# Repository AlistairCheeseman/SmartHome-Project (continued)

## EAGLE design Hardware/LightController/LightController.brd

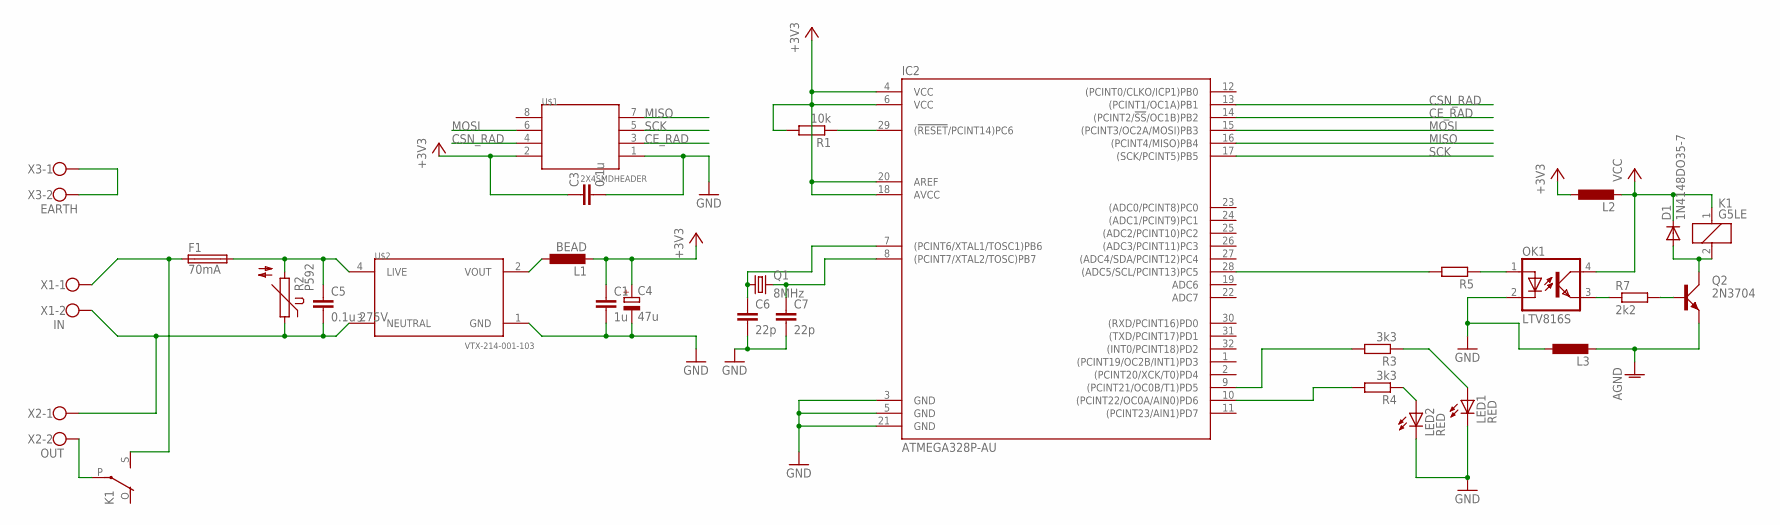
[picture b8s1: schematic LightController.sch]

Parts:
C1: 1u; C1206K
C3: 0.1u; C1206
C4: 47u; E2,5-6E
C5: 0.1u 275V; C15B5
C6, C7: 22p; C1206
D1: 1N4148DO35-7; DO35-7
F1: 70mA; SH22,5A
IC2: ATMEGA328P-AU; TQFP32-08
K1: G5LE
L1: BEAD; L3230M
L2, L3: L-EUL3230M; L3230M
LED1, LED2: RED; 1206
OK1: LTV816S; DIL4-SMD
Q1: 8MHz; HC49U70
Q2: 2N3704; TO92C
R1: 10k; R1206
R2: P592
R3, R4: 3k3; R1206
R5: R-EU_R1206; R1206
R7: 2k2; R1206
U$1: 2X4SMDHEADER; TSM-110-XX-XXX-DV
U$2: VTX-214-001-103; VTX214001103
X1: IN; W237-102
X2: OUT; W237-102
X3: EARTH; W237-102

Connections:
+3V3: C1.1, C3.1, C4.+, IC2.4 (VCC), IC2.6 (VCC), IC2.18 (AVCC), IC2.20 (AREF), L1.2, L2.1, R1.2, U$1.2
AGND: L3.2, Q2.E
CE_RAD: IC2.14 ((PCINT2/!SS!/OC1B)PB2), U$1.3
CSN_RAD: IC2.13 ((PCINT1/OC1A)PB1), U$1.4
GND: C1.2, C3.2, C4.-, C6.2, C7.2, IC2.3 (GND), IC2.5 (GND), IC2.21 (GND), L3.1, LED1.C, LED2.C, OK1.2 (C), U$1.1, U$2.1 (GND)
MISO: IC2.16 ((PCINT4/MISO)PB4), U$1.7
MOSI: IC2.15 ((PCINT3/OC2A/MOSI)PB3), U$1.6
unnamed: F1.1, K1.S, X1.1
unnamed: C5.1, F1.2, R2.2, U$2.4 (LIVE)
unnamed: IC2.29 ((!RESET!/PCINT14)PC6), R1.1
unnamed: C5.2, R2.1, U$2.3 (NEUTRAL), X1.2, X2.1
unnamed: IC2.10 ((PCINT22/OC0A/AIN0)PD6), R4.2
unnamed: LED1.A, R3.1
unnamed: IC2.28 ((ADC5/SCL/PCINT13)PC5), R5.2
unnamed: C6.1, IC2.7 ((PCINT6/XTAL1/TOSC1)PB6), Q1.1
unnamed: C7.1, IC2.8 ((PCINT7/XTAL2/TOSC)PB7), Q1.2
unnamed: LED2.A, R4.1
unnamed: OK1.1 (A), R5.1
unnamed: K1.P, X2.2
unnamed: X3.1, X3.2
unnamed: OK1.3 (EMIT), R7.1
unnamed: D1.A, K1.2, Q2.C
unnamed: Q2.B, R7.2
unnamed: IC2.9 ((PCINT21/OC0B/T1)PD5), R3.2
SCK: IC2.17 ((SCK/PCINT5)PB5), U$1.5
VCC: D1.C, K1.1, L2.2, OK1.4 (COL)
VOUT: L1.1, U$2.2 (VOUT)

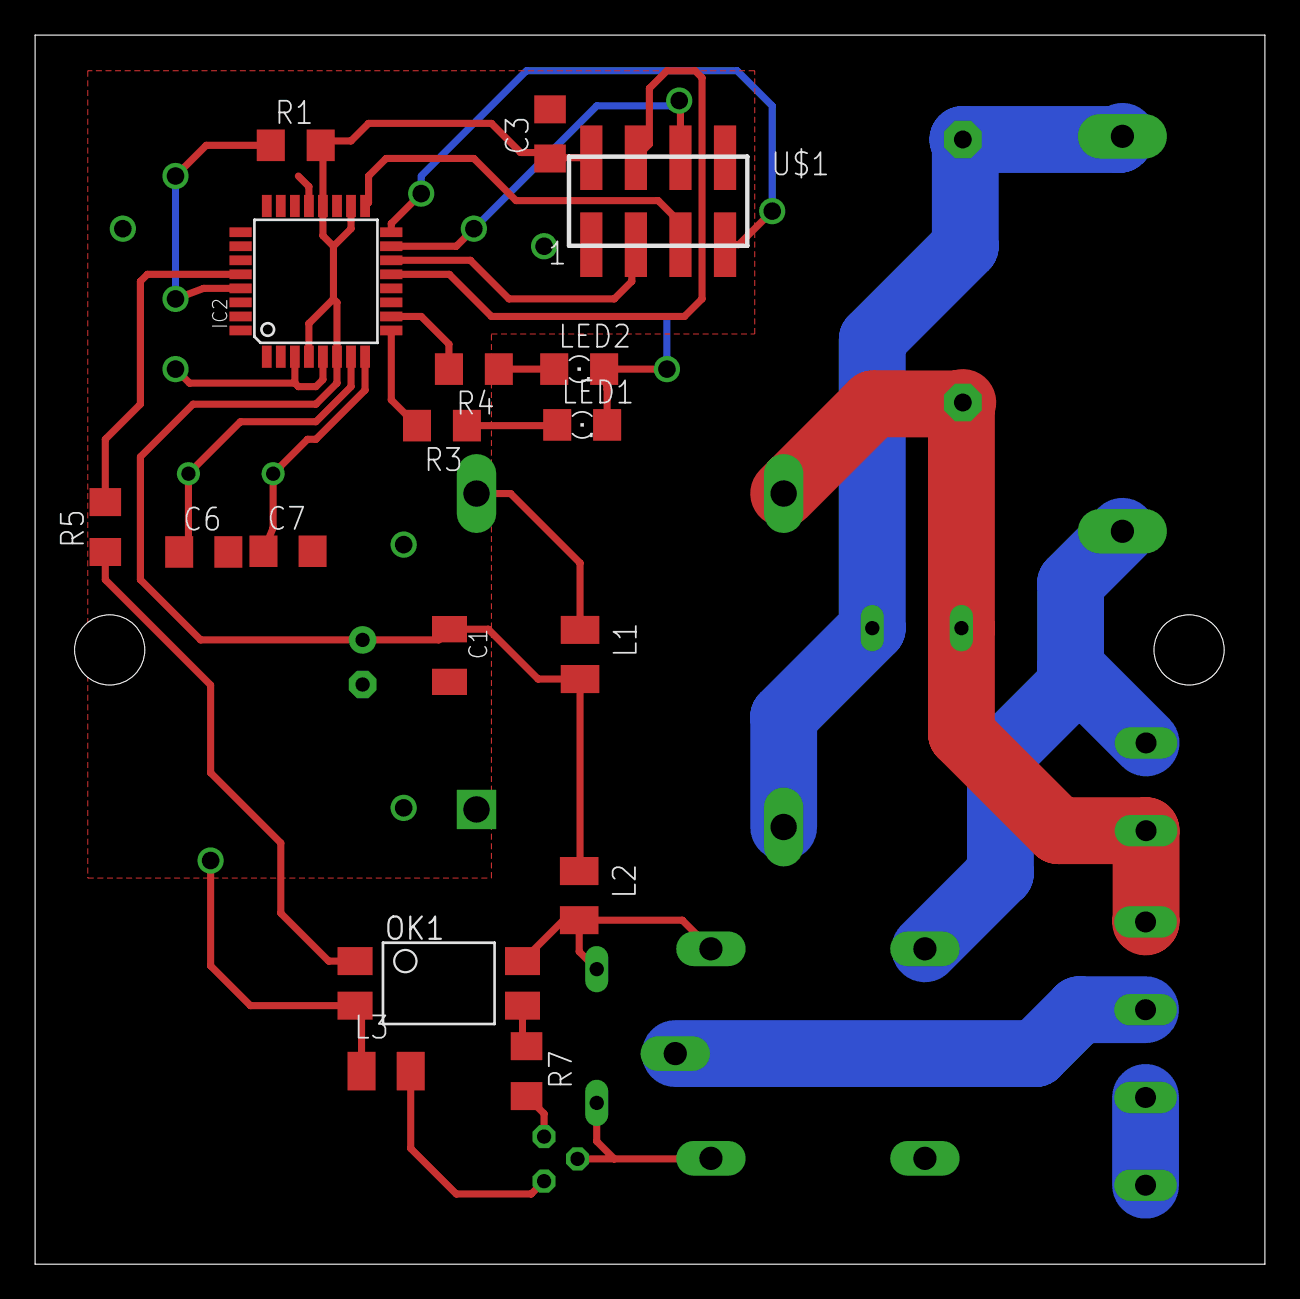
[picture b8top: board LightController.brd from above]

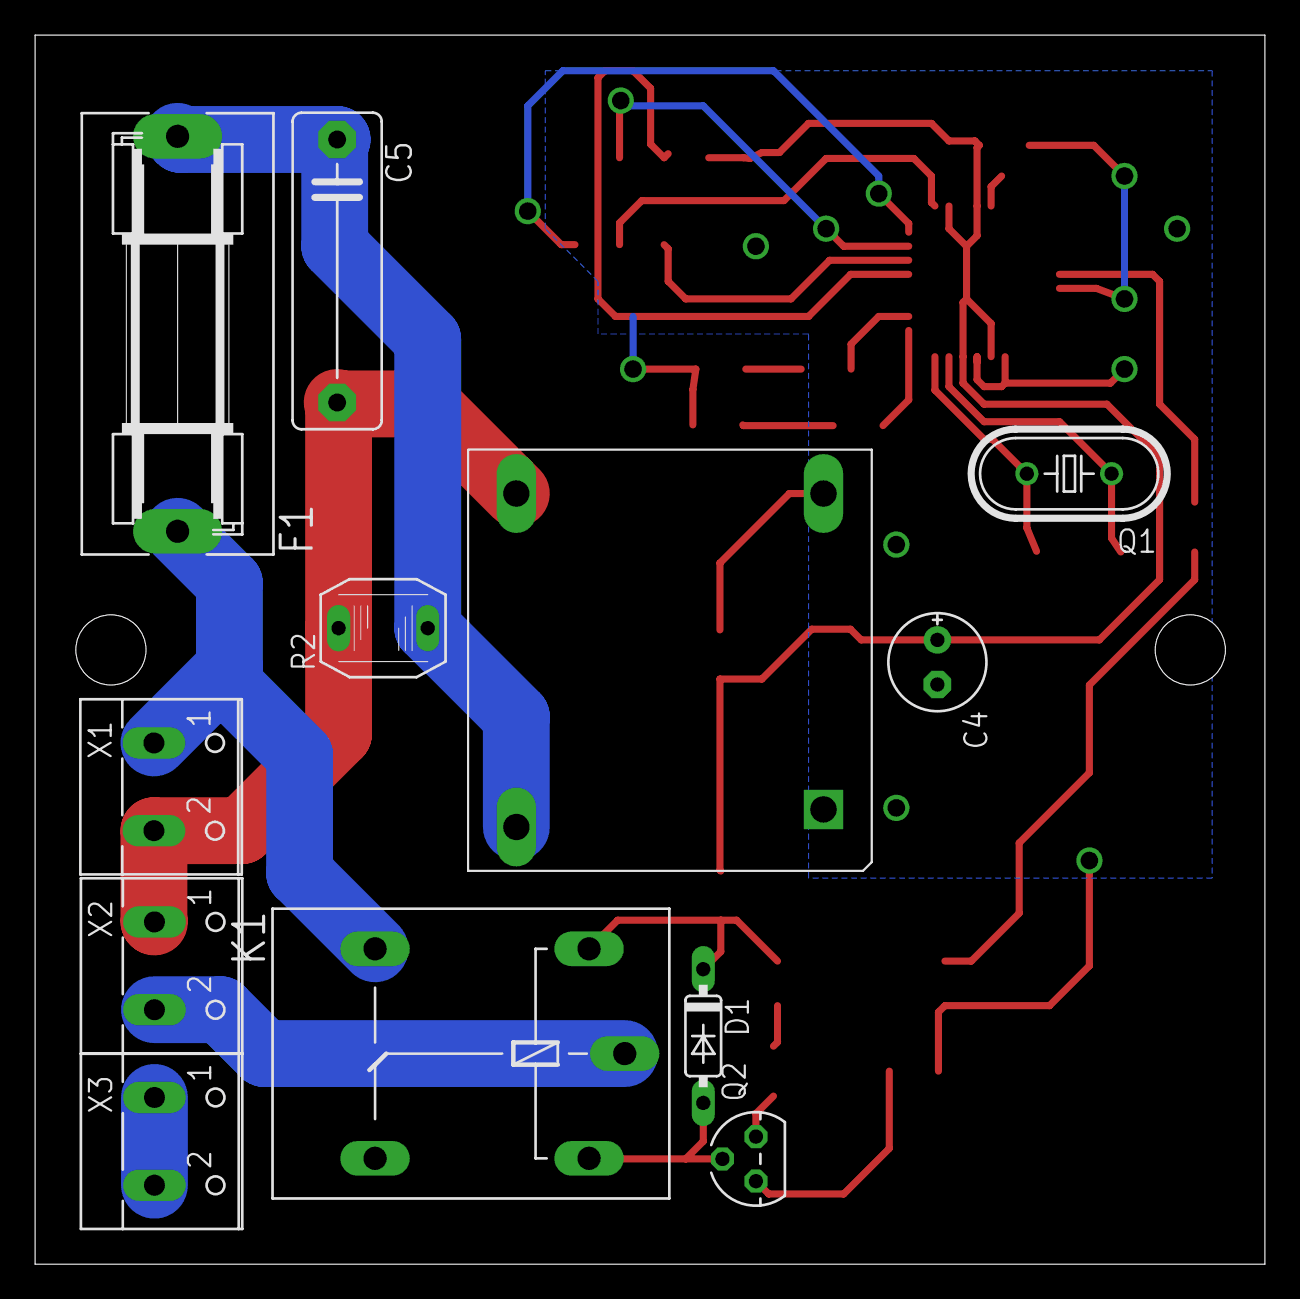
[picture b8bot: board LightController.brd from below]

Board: 2 copper layers, 70.1 x 70.0 mm, 29 parts (12 on the bottom side), 27 nets.

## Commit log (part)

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2014-12-04 Initial Commit of current PCBs
2014-12-08 Added Linux From Scratch (LFS) style build scripts and files. However the build scripts are found to be flawed.
2015-01-20 updated build scripts for a more automated procedure. Additionally applied new packages. However the build script is missing creation of a working SPI dtb. (see https://github.com/RobertCNelson/dtb-r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
2015-01-20 fixed mosquitto location on startup script. fixed script not setting executable on services fixed startupscript not setting LEDs to off
2015-01-25 removed files that were not meant to be added to git repo
2015-01-25 Updated PDF PCB files with Document outline mark. Fixed missing Name for NRF connector. Updated BOM to be correctly formatted.
2015-01-30 added php & apache packages. Still need to fix httpd being set with wrong directory location
2015-01-30 updated V2 ( Rev B) Board to use SMD only components where possible. Using 1206 Components
2015-02-01 Updated website to use SQLite. Sucessfully got graph pulling and rendering data from SQL
2015-02-01 added high power components for energy sensor. transformer needs to be sorted.
2015-02-01 created blank NRF program to work NRF wireless module ( added SPI and GPIO classes to handle hardware functions
2015-02-01 updated config to remove timezone error. Updated new value to prevent <1 values being refused.
2015-02-02 added simple start stop status restart however script still very lacking and due to be developed
2015-02-03 added marker to board file to allow for better silkscreen alignment
2015-02-06 added sqlite test program and sql classes
2015-02-06 added min value for power scale
2015-02-06 imporoved symbol
2015-02-06 initial mockup of heating controller
2015-02-06 created a programmer to allow for programming through the comms port
2015-02-12 updated to fix bug where spi would not fully work. due to other enabled devices.
2015-02-12 updated beaglebone cape and added pdf build files
2015-02-12 updated to fuse and varistor arrangements
2015-02-12 updated project files
2015-02-12 updated web layer to reflect logic layer changes
2015-02-12 added power outlet board
2015-02-12 updated git ignore files
2015-02-22 updated sql functions with new working sql schema
2015-02-22 updated styling for website and created base layer
2015-02-23 added basic components still awaiting Vreg and sensor devices
2015-02-23 Updated bug where script was in DOS format not NIX format
2015-02-23 fixed incorrect push. nfs and local files were mixed up
2015-02-23 fixed missing parenthesis
2015-02-24 Updated to make program take command line arguments correctly
2015-02-24 updated get_data to get a more diverse set of data
2015-02-27 updated wireless program to work as a simple two way UDP to Wireless bridge
2015-03-02 removed debug files and updated gitignore
2015-03-03 fixed bug where stated size and recieved size were mixed up
2015-03-03 added start up script for wireless bridge
2015-03-03 Updated to use new device notation for shorter topics
2015-03-03 updated output to allow for start-stop-daemon to be used.
2015-03-06 removed unneeded delays. added recieved message progcessing. fixed bug where packets would get lost. NOTE: this is due to network.tick being called by other functions when is should ONLY be called fr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
2015-03-09 added room listing populating by javascript (json ajax requests)
2015-03-10 Updated wrong fuse holder and processor footprint
2015-03-11 Updated issue where httpd would not find httpd headers
2015-03-11 updated to fix incorrect pin assignments
2015-03-11 updated to correct componnent values and minor tweaks
2015-03-11 updated moved to new revision as Rev A has already been produced. Added inductor to clean output power rail.
2015-03-11 updated BOM to match order
2015-03-12 updated web interface and added basic room & device functions
2015-03-13 added new library to correct incorrect footprint for LTV816S
2015-03-13 updated to list different categories of sensors (imporves readability)
2015-03-15 updated to prevent any caching of files
2015-03-15 added new library for 3.5mm jack
2015-03-16 updated component values
2015-03-16 updated gitignore to ignore AVR Firmware build files
2015-03-19 removed testing page to update variables
2015-03-20 Updated Rev B to reflect beneficial changes with Rev A pratical application, added noise suppressor to ARef. updated smoothing Ref Caps to match package. Added Additional Smoothing capacitors (due to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
2015-03-20 fixed dynamic power size message
2015-03-21 fixed typos on index page and added acknowledgements
2015-03-21 added a better printout (compressed more and HEX printing correctly (2 Digits per byte)
2015-03-21 added fix where packets would be massivley huge. Added increased client support to main()
2015-03-21 fixed incorrect resistor footprints. Added AGND Isolation Inductor. Added Silk Text. Moved Component Labels
2015-03-21 Renamed Lighting controller to lightswitch. Updated VTX supply text
2015-03-21 created mock up of Board
2015-03-22 initial mock up of lightswitch component placement
2015-03-22 updated etch and create TOP etch for print tests
2015-03-23 generated ETCH and RESIST Masks
2015-03-28 updated net css to use new styling from http://www.lavishbootstrap.com/. Added missing Sensor pages - (edit delete new). Added support to set a sensor request to have multiple destinations
2015-03-28 updated JSON PHP requests to match Web interface changes
2015-03-28 updated gitignore for future Apps
2015-03-28 fixed line spacing
2015-03-28 moved delay and increased to allow the delay to actually benefit the tick() function
2015-03-28 changed to get all message Ids on boot and publish to the ID rather than getting the Id then publishing, helped with response times. also sped up connects, as was missing connack packets due to delay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
2015-03-30 added simple packet routing ( hardcoded routing into program).
2015-03-31 added support for dynamic creation of addresses based on level and id.
2015-03-31 updated ignore to ignore .atsuo files
2015-03-31 fixed bug where if payload was bigger than 1 the packet would be chopped short.
2015-03-31 updated graph container name to match rest of website
2015-03-31 Fixed graph referencing. ( changed from container to sensorGraph) added suffix for power data for tooltip added processing of power compound data for set sensor types.
2015-03-31 created simple power measurement routine with calibrated sensors. still to add power angle support and real power calculations.
2015-03-31 changed the sensor history link to pass the control type aswell as the sensorid
2015-04-01 MASSIVE BUG - Listening on 000 and transmitting to it would cause messages to be sent all over the place. It turned out that the address is not an address of the device but and address of the COMMUNI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
2015-04-02 created initial schematic and basic component placements
2015-04-03 updated processoor to be surface mount. created intial route for pcb tracks. Had to use dual layer board to allow for small form factor
2015-04-03 fixed indentations, and changed wireless --> UDP wording to better show data direction changed to UDP <-- Wireless
2015-04-03 added little flash of lights at beginning and fixed indentation
2015-04-03 indented and added a timeout for waitResponse()
2015-04-03 moved datasheets into repository
2015-04-04 indented and swet graphs to use Area specific date times ( accounts for BST, GMT etc)
2015-04-04 now using the functions.js file to draw the power graph, modified the wording on the graph too
2015-04-04 added pdf of Etch layers.
2015-04-04 added 0 topicId checking to double check that the topicid is valid. topicid=0 if no response
2015-04-04 added code region to make common code hideable
2015-04-04 pragma region works in ide but breaks compile
2015-04-05 added heating controller header
2015-04-05 added simple heating controller code. ( note close copy of power outlet code)
2015-04-06 added board information text
2015-04-06 updated silk to Include hole patterns
2015-04-06 updated pdf to reflect postscript changes
2015-04-06 updated board text to be the correct way round
2015-04-07 included the calculations for the conversion from the values recieved from the sensor. ( referenced from datasheet) and changed read order.
2015-04-07 corrected filtering to work by control type category ( output, sensor, request)
2015-04-07 added temperature humidity and LUX to sensor History
2015-04-08 modified chart type of temperature sensor to give a smoother line.
2015-04-08 modified table to be accessible by javascript and removed sample data, and added javascript function to populate table
2015-04-08 added environment data view
2015-04-08 removed unnecessary udp connection and configured the additional client (5)
2015-04-09 moved javascript to show correct form for sensor data to sepearte function to enable the ability to call it manually which fixes bug where on ititial load the new sensor form would not show correct d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
2015-04-09 changed where onchange is called first time to update the default selection of the page. In old position it would cause the mapping list to be duplicated
2015-04-09 added delays between publish to allow server to process requests
2015-04-09 created basic working code
2015-04-09 added filter to only check for rules that can be processed by the scheduler
2015-04-09 updated Scheduler to put lastexec time into rule dbif rule is ran. also corrected filtering of what rules to process
2015-04-09 updated scheduler to delete temporary rules once they have been executed
2015-04-09 added delete page for rules
2015-04-09 fixed case for variables
2015-04-10 added sqlopen threaded access. added retry loop to log function. added more information to sql errors. Indented page correctly. merged some sql statements.
2015-04-16 added SQL commands to get sensorId and to get rule information
2015-04-16 fixed issue where RuleTypeId would not be loaded.
2015-05-07 updated BOM with finalised pricelist
2015-10-04 added version check script from CLFS website
2015-10-05 created buildscript that uses KMX mirror for sources
2015-10-05 updated rest of links to kmx server
2015-10-07 added check for lzop
2015-10-07 commit of some old changes that were missed from final commit
2015-10-17 added startup script for logiclayer to resources
2015-10-19 Added BC to version check
2016-01-09 started creation of RevC Beaglebone cape. - aims to add EEPROM programming capability and full support of any comms module
2016-01-09 added beaglebone black reference manual
2016-01-10 added fix to force 3.14 kernel build. also updated mirror location
2016-01-11 moved gitignore
2016-01-12 initial mockup of board layout, removed 8 pin connector in favour of the single-module board
2016-01-19 fixed hang on no arguments
2016-05-22 Update install-toolchain.sh
    added reminder to upgrade openssl version
2016-05-29 updated to new versions of files - totest
2016-07-03 Updated database generation script and added default values. updated the databaseexists to use an active table rather than a defunct table
2016-07-03 added netbeans files to gitignore
2016-07-03 updated board layout and exported svg files
2016-07-03 initial mockup of energysensor RevC
2016-07-10 moved energy sensor to nice case and various tweaks
2016-07-10 moved text and created exports for energy sensor
2016-08-05 fixed missing wire
2016-08-08 added lsdiff to version check
2016-08-09 added simple NFS/LOCAL switch and internal filestore mirror/direct option
2016-08-19 updated nameserver to be more generic
2016-08-19 created class to make logging simpler
2016-08-20 added global logging class to logiclayer made makefiles automatically source buildscript variables
2016-08-20 fixed missing makefile modifications to commit 02be7602c5a710074adab73ad601109a55723536
2016-08-20 added additonal files to gitignore
2016-11-01 Added support for GCC6 on the host to build and support for building mysql
2016-11-13 added missing finalise statement to SQL::GetRules
2016-11-14 changed to source relative buildscript rather than absolute buildscript
2016-11-18 moved all possible options to a common config file - to make changes easier to manage
2016-11-19 added large buffer for target topic payloads
2016-11-20 fixed bug trying to free already freed memory and added timeout to SQL connection to allow more reliable operation
2016-11-24 fixed TCF build and fixed up package commands
2016-11-24 fixed up makefiles to work on both native or cross builds
